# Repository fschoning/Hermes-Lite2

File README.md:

> **This fork: HL2 raw front end.** Experimental gateware that streams every raw ADC sample over the HL2's own
> gigabit Ethernet port, with a RISC-V CPU and a transmit interlock inside the FPGA. See the
> [release](https://github.com/fschoning/Hermes-Lite2/releases/tag/hl2-rawfront-release-v0.1),
> the [documentation](https://github.com/fschoning/Hermes-Lite2/blob/hl2-rawfront-release/docs/rawfront/README.md)
> and the [source branch](https://github.com/fschoning/Hermes-Lite2/tree/hl2-rawfront-release).

Hermes-Lite 2.x
===============

See the main [Hermes-Lite Web Page](http://www.hermeslite.com) for the latest links and details.

This is a work in progress to create a low-cost software defined amateur radio HF transceiver based on a [broadband modem chip](http://www.analog.com/en/broadband-products/broadband-codecs/ad9866/products/product.html) and the [Hermes SDR](http://openhpsdr.org/wiki/index.php?title=HERMES) project.

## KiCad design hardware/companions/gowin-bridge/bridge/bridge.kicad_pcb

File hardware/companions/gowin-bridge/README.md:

# gowin-bridge — Hermes Lite 2 SlimSAS bridge, rev D

**One design with two ends, on one board.** One schematic, one PCB, one BOM,
one project directory. The **radio end** plugs onto the Hermes-Lite 2; the
**Gowin end** plugs onto a Tang Mega 138K dock's J14. They are made together
and snapped apart. Two radio ends and one cable make a radio-to-radio link; a
radio end, a Gowin end and one cable make a radio-to-FPGA link.

The radio end:
A flat companion board that plugs onto the HL2's **DB1** (2×10), **DB12** (2×3)
and **CN1** (2×5 JTAG) headers and carries **one SlimSAS SFF-8654 8i
receptacle** on its front edge. A single $15 cable carries 16 differential
pairs and 16 sideband conductors.

| | |
|---|---|
| Board | radio end **64.50 × 64.88 mm**, 4 layer, 1.6 mm, HASL. HL2 x 70.00→134.50, y 73.37→138.25. The whole board, both ends, is **64.50 × 92.00 mm**, no rails, the ends joined by three mouse-bite tabs |
| Underside | 11.04 mm above the HL2's top surface (10.92 mm measured on the owner's radio), on 2.54 mm sockets and one M3 screw; holes over the radio's FPGA, AD9866 and T2 |
| Connector | Amphenol ICC **U10A474240T**, LCSC **C5432262** |
| Cable | 10Gtek **CAB-8654/8654-8i-P**, 8i to 8i, 0.5 m, **$15** |
| Lane rate | DDR at 153.6 MHz = **307.2 Mbit/s**, three lanes each way |
| Payload | **921.6 Mbit/s** each way = the complete raw 12-bit 76.8 MSPS ADC stream, plus a full-duplex auxiliary channel at the same rate |
| Parts | both ends: 184, of which **152 fitted**; 176 nets; **24 placed part numbers**, 16 Basic, 7 Extended and 1 Preferred Extended; eleven test points |
| Cost | **$162.43** for five assembled boards, both ends, delivered: **$32.49 per complete link** |
| State | schematic generated and validated; **prepared for Quilter**: fixed parts locked, everything else waiting off the board (`QUILTER.md`); **not placed, not routed** |

---

## The documents, and which to read first

| | |
|---|---|
| **`STATUS.md`** | **Start here.** What is built, what changed from rev C and why, the four numbers that were blocking the order, three corrections to the brief, six deliberate departures from it, everything unverified, and the next steps in order |
| `PINMAP.md` | **The pin contract.** Every HL2 header pin, all 74 connector contacts, the crossover, the lane and sideband maps, the AUXIO group, the enables, and the paste-ready Quartus block. Authoritative; `tools/check_netlist.py` asserts it |
| `DESIGN_NOTES.md` | Why, with the numbers. Data rates, the 2.5 V threshold problem and the part that does not exist, termination and edge rates, **the power budget**, **the ESD decision**, the mechanical argument, parts sourcing, the JTAG contention answer, and everything unverified |
| `COST.md` | The order total in the categories the fab actually bills, what could be cut and what it saves, and what is not verified in the numbers |
| `ROUTING.md` | The routing rules for whoever lays this out, in the order they matter |

---

## Files

```
bridge/                 the ONE KiCad project
  bridge.kicad_sch      schematic, ERC 0 violations
  bridge.kicad_pcb      fixed parts locked, the rest staged off the board;
                        placement regions and keepouts; DRC 0, parity 0
  bridge.kicad_pro      project file, with the differentialpair and Power
                        net classes
quilter-upload/         the three KiCad 10 files to upload to Quilter
  bridge-bom.csv        BOM with LCSC numbers and a Populate column
  gowin-bridge.kicad_sym, gowin-bridge.pretty/   project-local libraries
templates/              1:1 print templates for offering up to the radio
panel-endcap/           the re-cut front end panel - SEE THE WARNING BELOW
tools/
  gen_gowin_bridge.py   generates everything above from one netlist description
  check_netlist.py      asserts the pin maps, the crossover and the safety props
  check_geometry.py     asserts the locked parts, the land patterns and,
                        on a returned board, the placement and routing rules
  cost_model.py         computes the order total from the generated BOM and PCB
  kisexp.py             the KiCad s-expression reader/writer
```

**Anything that changes a net must be changed in `tools/gen_gowin_bridge.py`
and regenerated, never hand-edited in the KiCad files, and `PINMAP.md` must be
updated in the same commit.**

## To rebuild and validate

```
cd hardware/companions/gowin-bridge
python tools/gen_gowin_bridge.py
python tools/check_geometry.py     # must print OK
python tools/check_netlist.py      # must print OK
python tools/cost_model.py         # the order total
# bridge/bridge.kicad_dru is picked up by DRC: fast nets 3 mm from every edge

set KC=C:\Users\franz\AppData\Local\Programs\KiCad\10.0\bin\kicad-cli.exe
%KC% sch erc --severity-error -o bridge/bridge-erc.rpt bridge/bridge.kicad_sch
%KC% pcb drc --severity-error --schematic-parity --refill-zones ^
     -o bridge/bridge-drc.rpt bridge/bridge.kicad_pcb
```

---

## The front end panel

`panel-endcap/panel-endcap.kicad_pcb` (55 mm case, rev C) has the SlimSAS
opening at **panel x 120.30–144.30 = HL2 y 107.30–131.30**, centred on the
connector, 24.00 × 10.40 mm at 12.39–22.79 mm above the HL2's top surface.
Nine stock vent holes had to go where the opening landed; nine were put back
above it on 13 Sep 2026, so the vent area is the stock 73.7 mm². Order it
separately as a bare PCB. `G:/proj/Hermes-Lite2/franz-claude-analysis/HL2_END_PANEL.md`
has the derivation, clearances and strength check.

**Not compatible:** the repo's DB9 adapter board (`hardware/companions/db9/`)
cannot be fitted with this board; its wires land on DB1 pins our socket
covers. Run a Hardrock-50 from the N2ADR HL2 IO board instead
(`DESIGN_NOTES.md` §14.7).

## The Gowin end

A passive board: the same SlimSAS connector, 12 ESD arrays, 9 resistors and a
hand-fitted 2×18 onto J14 positions 5–40. Bank 4 of the Gowin FPGA drives and
receives true LVDS at its 3.3 V supply. Placed at the 40 mm case position.
`PINMAP.md` §11, `DESIGN_NOTES.md` §11, `gowin_end_j14.cst`.

## To order

JLCPCB, **Economic** assembly, **5 boards**, 4 layer, 1.6 mm, lead-free HASL,
green, 1 oz, delivered as a single PCB with the tabs unbroken. It is one
64.50 × 92.00 mm board with one outline and no rails; the two ends are joined
by three mouse-bite tabs. Ask JLCPCB first whether that counts as one design
(`DESIGN_NOTES.md` §13.2). Do not buy impedance control — `COST.md` §4 explains why.
`COST.md` §1 is the line-by-line.

Then hand-solder, per board: the DB1 2×10 socket and the DB12 2×3 socket and
the CN1 2×5 socket on the **underside**, the JTAG pass-through 2×5 header on
the **top**, and **the connector's four 2.2 mm shell tails**.

**Before any of that, buy one cable and ohmmeter it.** The whole one-design
argument rests on the cable crossing row A onto row B, and 10Gtek publish no
wiring diagram for this part. `STATUS.md` has the test.

**And do not fit or remove the board with the radio powered** — the hot-plug
inrush is about 22 A for 3.3 µs. It is on the silkscreen.

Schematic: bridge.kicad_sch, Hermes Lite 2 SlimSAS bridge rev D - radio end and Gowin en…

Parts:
C1, C2, C3, C4, C5, C6, C7, C8, C9, C10, C11, C12, C13, C14, C15, C16, C17, C18, C19, C21, C22, C23: 100nF; C_0402_1005Metric; LCSC C1525
C20: 1uF; C_0402_1005Metric; LCSC C52923
C24, C25, C26: 10uF; C_0805_2012Metric; LCSC C15850
C27: 10pF; C_0402_1005Metric; LCSC C32949
C28: 10nF; C_0402_1005Metric; LCSC C15195
C29: 100uF; CP_EIA-3528-21_Kemet-B; LCSC C16133
C30, C101: 10nF; C_0805_2012Metric; LCSC C1710; not fitted
D1, D2, D3, D4, D5, D6, D7, D8, D9, D10, D11, D12, D101, D102, D103, D104, D105, D106, D107, D108, D109, D110, D111, D112: TPD4E05U06; USON-10_2.5x1.0mm_P0.5mm; LCSC C138714
D13, D14: RB751V-40; D_SOD-323; LCSC C7502691
FB1: 120R/2A; L_0603_1608Metric; LCSC C14709
FB2: 120R/2A; L_0603_1608Metric; LCSC C14709; not fitted
FID1, FID2, FID3: Fiducial; Fiducial_1mm_Mask2mm
J1: SlimSAS 8i 74P R/A; SlimSAS_SFF-8654_8i_74P_RightAngle; LCSC C5432262
J2: DB1 2x10 socket; PinSocket_2x10_P2.54mm_Vertical; not fitted
J3: DB12 2x03 socket; PinSocket_2x03_P2.54mm_Vertical; not fitted
J4: CN1 2x05 socket; PinSocket_2x05_P2.54mm_Vertical; not fitted
J5: JTAG pass-through; PinHeader_2x05_P2.54mm_Vertical; not fitted
J101: SlimSAS 8i 74P R/A; SlimSAS_SFF-8654_8i_74P_RightAngle_M3; LCSC C5432262
J102: TANG J14 pos 5-40, 2x18; PinSocket_2x18_P2.54mm_Vertical; not fitted
L1: 4.7uH; L_Sunlord_SWPA4030S; LCSC C193025
Q1, Q2, Q3, Q4, Q5, Q6: AO3400A; SOT-23; LCSC C20917
R1, R37, R38, R39, R40, R41, R42, R43, R44: 100R; R_0402_1005Metric; LCSC C25076
R2: 470R; R_0402_1005Metric; LCSC C25117
R3, R4, R5, R6, R7, R8, R9, R10, R104, R106, R107, R108: 330R; R_0402_1005Metric; LCSC C25104
R11, R12, R13, R14, R15, R16, R17, R18, R19, R20, R28, R29, R30, R31, R32, R33, R34, R35, R36, R46, R47, R48, R49, R50, R51, R52, R102, R103, R109: 10k; R_0402_1005Metric; LCSC C25744
R21: 1k; R_0402_1005Metric; LCSC C11702; not fitted
R22, R23, R24, R25, R26: 0R; R_0402_1005Metric; LCSC C17168
R27, R101, R105: 1k; R_0402_1005Metric; LCSC C11702
R45: 100k; R_0402_1005Metric; LCSC C25741
R110, R111, R112, R113, R114, R115, R116: 100R; R_0402_1005Metric; LCSC C25076; not fitted
R117: 0R; R_0805_2012Metric; LCSC C17477
R_CLKSEL_A: 0R; R_0402_1005Metric; LCSC C17168
R_CLKSEL_B: 0R; R_0402_1005Metric; LCSC C17168; not fitted
R_DRVEN_ON: 0R; R_0402_1005Metric; LCSC C17168; not fitted
R_DRVEN_PRSNT: 0R; R_0402_1005Metric; LCSC C17168
R_LBYP: 0R; R_0805_2012Metric; LCSC C17477; not fitted
R_SHELL: 0R; R_0805_2012Metric; LCSC C17477
SL_VLVDS: 0R; R_0402_1005Metric; LCSC C17168; not fitted
TP1: TP_+3V3; TestPoint_Pad_D1.5mm
TP2: TP_+2V5; TestPoint_Pad_D1.5mm
TP3: TP_SB_PRSNT_IN; TestPoint_Pad_D1.5mm
TP4: TP_JTAG_EN_N; TestPoint_Pad_D1.5mm
TP5: TP_AUXIO_EN_N; TestPoint_Pad_D1.5mm
TP6: TP_AUXIO_OE_N; TestPoint_Pad_D1.5mm
TP7: TP_HL2_FWD_CLK; TestPoint_Pad_D1.5mm
TP8: TP_HL2_REV_CLK; TestPoint_Pad_D1.5mm
TP9: TP_GND; TestPoint_THTPad_D2.0mm_Drill1.0mm
TP10: TP_LINK_ALIVE; TestPoint_Pad_D1.5mm
TP101: TP_G_GND; TestPoint_THTPad_D2.0mm_Drill1.0mm
U1, U2, U3, U8, U9, U10, U11: SN74AVC4T245PW; TSSOP-16_4.4x5mm_P0.65mm; LCSC C81461
U4, U5: DS90LV047A; SOIC-16_3.9x9.9mm_P1.27mm; LCSC C206491
U6, U7: DS90LV048A; TSSOP-16_4.4x5mm_P0.65mm; LCSC C87137
U12: ME6211C25M5G; SOT-23-5; LCSC C194395

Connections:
+2V5: C1.1, C3.1, C6.1, C20.1, C23.1, C25.1, R16.2, R18.2, SL_VLVDS.2, TP2.1, U1.1 (VCCA), U1.2 (1DIR), U1.3 (2DIR), U2.1 (VCCA), U2.2 (1DIR), U2.3 (2DIR), U3.16 (VCCB), U12.5 (V_{OUT})
+3V3: C2.1, C4.1, C5.1, C7.1, C8.1, C9.1, C10.1, C11.1, C12.1, C13.1, C14.1, C15.1, C16.1, C17.1, C18.1, C19.1, C22.1, C24.1, C29.1, L1.2, R17.2, R19.2, R20.2, R27.2, R30.2, R32.2, R33.2, R34.2, R35.2, R46.2, R47.2, R48.2, R_DRVEN_ON.2, R_LBYP.2, TP1.1, U1.16 (VCCB), U2.16 (VCCB), U3.1 (VCCA), U3.2 (1DIR), U3.3 (2DIR), U4.4 (VCC), U5.4 (VCC), U6.13 (VCC), U6.16 (EN), U7.13 (VCC), U7.16 (EN), U8.1 (VCCA), U8.2 (1DIR), U8.3 (2DIR), U8.16 (VCCB), U9.1 (VCCA), U9.2 (1DIR), U9.3 (2DIR), U9.16 (VCCB), U10.1 (VCCA), U10.2 (1DIR), U10.3 (2DIR), U10.16 (VCCB), U11.1 (VCCA), U11.2 (1DIR), U11.3 (2DIR), U11.16 (VCCB), U12.1 (V_{IN}), U12.3 (CE)
AUXIO0_T: R3.2, U8.4 (1A1), U9.13 (1B1)
AUXIO1_T: R4.2, U8.5 (1A2), U9.12 (1B2)
AUXIO2_T: R5.2, U8.6 (2A1), U9.11 (2B1)
AUXIO3_T: R6.2, U8.7 (2A2), U9.10 (2B2)
AUXIO_EN_LA_N: Q1.2 (S), Q4.3 (D)
AUXIO_EN_N: Q4.2 (S), R19.1, TP5.1, U2.10 (2B2)
AUXIO_OE_N: Q1.3 (D), R20.1, TP6.1, U9.14 (2~OE), U9.15 (1~OE)
A_ADCD0_N: D4.2 (D1-), J1.A18, U4.13 (DOUT2-)
A_ADCD0_P: D4.1 (D1+), J1.A17, U4.14 (DOUT2+)
A_ADCD1_N: D5.2 (D1-), J1.A21, U4.12 (DOUT3-)
A_ADCD1_P: D5.1 (D1+), J1.A20, U4.11 (DOUT3+)
A_ADCD2_N: D6.2 (D1-), J1.A24, U4.9 (DOUT4-)
A_ADCD2_P: D6.1 (D1+), J1.A23, U4.10 (DOUT4+)
A_AUXCLK_N: D1.2 (D1-), J1.A3, U5.13 (DOUT2-)
A_AUXCLK_P: D1.1 (D1+), J1.A2, U5.14 (DOUT2+)
A_AUXDAT_N: D2.2 (D1-), J1.A6, U5.12 (DOUT3-)
A_AUXDAT_P: D2.1 (D1+), J1.A5, U5.11 (DOUT3+)
A_DUPCLK_N: D7.2 (D1-), J1.A33, U5.16 (DOUT1-)
A_DUPCLK_P: D7.1 (D1+), J1.A32, U5.15 (DOUT1+)
A_FWDCLK_N: D3.2 (D1-), J1.A15, U4.16 (DOUT1-)
A_FWDCLK_P: D3.1 (D1+), J1.A14, U4.15 (DOUT1+)
A_SPARE_N: D8.2 (D1-), J1.A36, U5.9 (DOUT4-)
A_SPARE_P: D8.1 (D1+), J1.A35, U5.10 (DOUT4+)
B_AUXCLK_N: D1.5 (D2-), J1.B3, R37.2, U7.4 (RIN2-)
B_AUXCLK_P: D1.4 (D2+), J1.B2, R37.1, U7.3 (RIN2+)
B_AUXDAT_N: D2.5 (D2-), J1.B6, R38.2, U7.5 (RIN3-)
B_AUXDAT_P: D2.4 (D2+), J1.B5, R38.1, U7.6 (RIN3+)
B_DUPCLK_N: D7.5 (D2-), J1.B33, R43.2, U7.1 (RIN1-)
B_DUPCLK_P: D7.4 (D2+), J1.B32, R43.1, U7.2 (RIN1+)
B_REVCLK_N: D3.5 (D2-), J1.B15, R39.2, U6.1 (RIN1-)
B_REVCLK_P: D3.4 (D2+), J1.B14, R39.1, U6.2 (RIN1+)
B_SPARE_N: D8.5 (D2-), J1.B36, R44.2, U7.8 (RIN4-)
B_SPARE_P: D8.4 (D2+), J1.B35, R44.1, U7.7 (RIN4+)
B_TXD0_N: D4.5 (D2-), J1.B18, R40.2, U6.4 (RIN2-)
B_TXD0_P: D4.4 (D2+), J1.B17, R40.1, U6.3 (RIN2+)
B_TXD1_N: D5.5 (D2-), J1.B21, R41.2, U6.5 (RIN3-)
B_TXD1_P: D5.4 (D2+), J1.B20, R41.1, U6.6 (RIN3+)
B_TXD2_N: D6.5 (D2-), J1.B24, R42.2, U6.8 (RIN4-)
B_TXD2_P: D6.4 (D2+), J1.B23, R42.1, U6.7 (RIN4+)
CN1_NC6: J4.6, J5.6
CN1_NC7: J4.7, J5.7
CN1_NC8: J4.8, J5.8
CN1_VTREF: J4.4, J5.4
DB1_3V3: C21.1, C26.1, FB1.1, J2.19, J2.20
DI_ADCD0: U1.12 (1B2), U4.3 (DIN2)
DI_ADCD1: U1.11 (2B1), U4.6 (DIN3)
DI_ADCD2: U1.10 (2B2), U4.7 (DIN4)
DI_AUXCLK: U2.13 (1B1), U5.3 (DIN2)
DI_AUXDAT: U2.12 (1B2), U5.6 (DIN3)
DI_FWDCLK: U1.13 (1B1), U4.2 (DIN1), U5.2 (DIN1), U11.6 (2A1)
DI_SPARE: R36.1, U5.7 (DIN4)
DRV_EN: R_DRVEN_ON.1, R_DRVEN_PRSNT.1, U4.1 (EN), U5.1 (EN)
GND: C1.2, C2.2, C3.2, C4.2, C5.2, C6.2, C7.2, C8.2, C9.2, C10.2, C11.2, C12.2, C13.2, C14.2, C15.2, C16.2, C17.2, C18.2, C19.2, C20.2, C21.2, C22.2, C23.2, C24.2, C25.2, C26.2, C28.2, C29.2, C30.2, D1.3 (GND), D1.8 (GND), D2.3 (GND), D2.8 (GND), D3.3 (GND), D3.8 (GND), D4.3 (GND), D4.8 (GND), D5.3 (GND), D5.8 (GND), D6.3 (GND), D6.8 (GND), D7.3 (GND), D7.8 (GND), D8.3 (GND), D8.8 (GND), D9.3 (GND), D9.8 (GND), D10.3 (GND), D10.8 (GND), D11.3 (GND), D11.8 (GND), D12.3 (GND), D12.8 (GND), D13.2 (A), J1.A1, J1.A4, J1.A7, J1.A10, J1.A13, J1.A16, J1.A19, J1.A22, J1.A25, J1.A28, J1.A31, J1.A34, J1.A37, J1.B1, J1.B4, J1.B7, J1.B10, J1.B13, J1.B16, J1.B19, J1.B22, J1.B25, J1.B28, J1.B31, J1.B34, J1.B37, J2.13, J2.14, J3.3, J3.4, J4.2, J4.10, J5.2, J5.10, Q2.2 (S), Q5.2 (S), Q6.2 (S), R2.2, R11.2, R12.2, R13.2, R14.2, R15.2, R21.2, R28.2, R29.2, R31.2, R36.2, R45.2, R49.2, R50.2, R51.2, R52.2, R_SHELL.2, TP9.1, U1.8 (GND), U1.9 (GND), U1.14 (2~OE), U1.15 (1~OE), U2.8 (GND), U2.9 (GND), U2.14 (2~OE), U2.15 (1~OE), U3.8 (GND), U3.9 (GND), U4.5 (GND), U4.8 (~EN), U5.5 (GND), U5.8 (~EN), U6.12 (GND), U7.12 (GND), U8.8 (GND), U8.9 (GND), U9.8 (GND), U9.9 (GND), U10.5 (1A2), U10.8 (GND), U10.9 (GND), U11.5 (1A2), U11.7 (2A2), U11.8 (GND), U11.9 (GND), U11.14 (2~OE), U12.2 (V_{SS})
G_A_AUXCLK_N: D101.2 (D1-), J101.A3, J102.23
G_A_AUXCLK_P: D101.1 (D1+), J101.A2, J102.24
G_A_AUXDAT_N: D102.2 (D1-), J101.A6, J102.17
G_A_AUXDAT_P: D102.1 (D1+), J101.A5, J102.18
G_A_DUPCLK_N: D107.2 (D1-), J101.A33, J102.1
G_A_DUPCLK_P: D107.1 (D1+), J101.A32, J102.2
G_A_REVCLK_N: D103.2 (D1-), J101.A15, J102.5
G_A_REVCLK_P: D103.1 (D1+), J101.A14, J102.6
G_A_SPARE_N: D108.2 (D1-), J101.A36
G_A_SPARE_P: D108.1 (D1+), J101.A35
G_A_TXD0_N: D104.2 (D1-), J101.A18, J102.31
G_A_TXD0_P: D104.1 (D1+), J101.A17, J102.32
G_A_TXD1_N: D105.2 (D1-), J101.A21, J102.33
G_A_TXD1_P: D105.1 (D1+), J101.A20, J102.34
G_A_TXD2_N: D106.2 (D1-), J101.A24, J102.35
G_A_TXD2_P: D106.1 (D1+), J101.A23, J102.36
G_B_ADCD0_N: D104.5 (D2-), J101.B18, J102.13, R113.2
G_B_ADCD0_P: D104.4 (D2+), J101.B17, J102.14, R113.1
G_B_ADCD1_N: D105.5 (D2-), J101.B21, J102.11, R114.2
G_B_ADCD1_P: D105.4 (D2+), J101.B20, J102.12, R114.1
G_B_ADCD2_N: D106.5 (D2-), J101.B24, J102.9, R115.2
G_B_ADCD2_P: D106.4 (D2+), J101.B23, J102.10, R115.1
G_B_AUXCLK_N: D101.5 (D2-), J101.B3, J102.19, R110.2
G_B_AUXCLK_P: D101.4 (D2+), J101.B2, J102.20, R110.1
G_B_AUXDAT_N: D102.5 (D2-), J101.B6, J102.21, R111.2
G_B_AUXDAT_P: D102.4 (D2+), J101.B5, J102.22, R111.1
G_B_DUPCLK_N: D107.5 (D2-), J101.B33, J102.27, R116.2
G_B_DUPCLK_P: D107.4 (D2+), J101.B32, J102.28, R116.1
G_B_FWDCLK_N: D103.5 (D2-), J101.B15, J102.15, R112.2
G_B_FWDCLK_P: D103.4 (D2+), J101.B14, J102.16, R112.1
G_B_SPARE_N: D108.5 (D2-), J101.B36
G_B_SPARE_P: D108.4 (D2+), J101.B35
G_GND: C101.2, D101.3 (GND), D101.8 (GND), D102.3 (GND), D102.8 (GND), D103.3 (GND), D103.8 (GND), D104.3 (GND), D104.8 (GND), D105.3 (GND), D105.8 (GND), D106.3 (GND), D106.8 (GND), D107.3 (GND), D107.8 (GND), D108.3 (GND), D108.8 (GND), D109.3 (GND), D109.8 (GND), D110.3 (GND), D110.8 (GND), D111.3 (GND), D111.8 (GND), D112.3 (GND), D112.8 (GND), J101.A1, J101.A4, J101.A7, J101.A10, J101.A13, J101.A16, J101.A19, J101.A22, J101.A25, J101.A28, J101.A31, J101.A34, J101.A37, J101.B1, J101.B4, J101.B7, J101.B10, J101.B13, J101.B16, J101.B19, J101.B22, J101.B25, J101.B28, J101.B31, J101.B34, J101.B37, J102.8, R102.2, R105.2, R109.2, R117.2, TP101.1
G_PRSNT_DRV: J102.26, R101.1
G_PRSNT_RD: J102.25, R103.2
G_SB_NC_A11: D110.1 (D1+), J101.A11
G_SB_NC_A12: D110.4 (D2+), J101.A12
G_SB_NC_A26: D111.1 (D1+), J101.A26
G_SB_NC_A27: D111.4 (D2+), J101.A27
G_SB_NC_B9: D109.5 (D2-), J101.B9
G_SB_NC_B11: D110.2 (D1-), J101.B11
G_SB_NC_B12: D110.5 (D2-), J101.B12
G_SB_NC_B26: D111.2 (D1-), J101.B26
G_SB_NC_B27: D111.5 (D2-), J101.B27
G_SB_NC_B29: D112.2 (D1-), J101.B29
G_SB_PRSNT_IN: D109.2 (D1-), J101.B8, R102.1, R103.1
G_SB_PRSNT_OUT: D109.1 (D1+), J101.A8, R101.2
G_SB_TCK_OUT: D109.4 (D2+), J101.A9, R104.2
G_SB_TDI_OUT: D112.4 (D2+), J101.A30, R107.2
G_SB_TDO_IN: D112.5 (D2-), J101.B30, R108.1, R109.1
G_SB_TMS_OUT: D112.1 (D1+), J101.A29, R106.2
G_SHELL: C101.1, J101.SH1 (SHELL1), J101.SH2 (SHELL2), J101.SH3 (SHELL3), J101.SH4 (SHELL4), R117.1
G_TCK_DRV: J102.30, R104.1, R105.1
G_TDI_DRV: J102.29, R107.1
G_TDO_RD: J102.3, R108.2
G_TMS_DRV: J102.4, R106.1
HL2_ADC_D0: J2.2, R11.1, U1.5 (1A2)
HL2_ADC_D1: J2.3, R12.1, U1.6 (2A1)
HL2_ADC_D2: J2.5, R13.1, U1.7 (2A2)
HL2_AUXIO_EN: J2.1, R18.1, U2.7 (2A2)
HL2_AUX_CLK_IN: J3.5, R22.2
HL2_AUX_CLK_OUT: J2.6, R14.1, U2.4 (1A1)
HL2_AUX_DAT_IN: J3.2, R23.2
HL2_AUX_DAT_OUT: J3.1, R15.1, U2.5 (1A2)
HL2_CWR: J2.10, R3.1
HL2_CWT: J2.12, R4.1
HL2_FWD_CLK: R1.2, R2.1, TP7.1, U1.4 (1A1)
HL2_FWD_CLK_RAW: J2.9, R1.1
HL2_JTAG_EN: J2.4, R16.1, U2.6 (2A1)
HL2_REV_CLK: J3.6, R_CLKSEL_A.2, R_CLKSEL_B.2, TP8.1
HL2_SCL1: J2.16, R5.1
HL2_SDA1: J2.18, R6.1
HL2_TX_D0: J2.11, R24.2
HL2_TX_D1: J2.15, R25.2
HL2_TX_D2: J2.17, R26.2
JTAG_EN_N: Q3.3 (D), R17.1, R21.1, TP4.1, U10.14 (2~OE), U11.15 (1~OE)
JTAG_EN_RAW_N: Q3.2 (S), U2.11 (2B1)
J_TCK: J4.1, J5.1, R7.2
J_TDI: J4.9, J5.9, R9.2
J_TDO: J4.3, J5.3, R10.1
J_TDO_T: R10.2, R48.1, U10.4 (1A1)
J_TMS: J4.5, J5.5, R8.2
LA_CLK: C27.1, U11.11 (2B1)
LA_PUMP: C27.2, D13.1 (K), D14.2 (A)
LINK_ALIVE: C28.1, D14.1 (K), Q2.1 (G), Q3.1 (G), Q4.1 (G), Q6.3 (D), R45.1, TP10.1
P3V3_FB: FB1.2, L1.1, R_LBYP.1
PRSNT_OE_N: Q5.3 (D), Q6.1 (G), R47.1, U8.14 (2~OE), U8.15 (1~OE), U10.15 (1~OE)
RX_AUXCLK: R51.1, U3.6 (2A1), U7.14 (ROUT2)
RX_AUXDAT: R52.1, U3.7 (2A2), U7.11 (ROUT3)
RX_DUPCLK: R50.1, U3.5 (1A2), U7.15 (ROUT1)
RX_EN_N: Q2.3 (D), R46.1, U3.14 (2~OE), U3.15 (1~OE), U6.9 (~EN), U7.9 (~EN)
RX_REVCLK: R49.1, U3.4 (1A1), U6.15 (ROUT1)
RX_TXD0: R24.1, U6.14 (ROUT2)
RX_TXD1: R25.1, U6.11 (ROUT3)
RX_TXD2: R26.1, U6.10 (ROUT4)
SB_AUXIO0_IN: D10.2 (D1-), J1.B11, R32.1, U9.4 (1A1)
SB_AUXIO0_OUT: D10.1 (D1+), J1.A11, U8.13 (1B1)
SB_AUXIO1_IN: D10.5 (D2-), J1.B12, R33.1, U9.5 (1A2)
SB_AUXIO1_OUT: D10.4 (D2+), J1.A12, U8.12 (1B2)
SB_AUXIO2_IN: D11.2 (D1-), J1.B26, R34.1, U9.6 (2A1)
SB_AUXIO2_OUT: D11.1 (D1+), J1.A26, U8.11 (2B1)
SB_AUXIO3_IN: D11.5 (D2-), J1.B27, R35.1, U9.7 (2A2)
SB_AUXIO3_OUT: D11.4 (D2+), J1.A27, U8.10 (2B2)
SB_NC9: D9.4 (D2+), J1.A9
SB_NC29: D12.1 (D1+), J1.A29
SB_PRSNT_IN: D9.2 (D1-), J1.B8, Q1.1 (G), Q5.1 (G), R28.1, R_DRVEN_PRSNT.2, TP3.1
SB_PRSNT_OUT: D9.1 (D1+), J1.A8, R27.1
SB_TCK_IN: D9.5 (D2-), J1.B9, R29.1, U10.6 (2A1)
SB_TCK_IN_B: R7.1, U10.11 (2B1)
SB_TDI_IN: D12.5 (D2-), J1.B30, R31.1, U11.4 (1A1)
SB_TDI_IN_B: R9.1, U11.13 (1B1)
SB_TDO_OUT: D12.4 (D2+), J1.A30, U10.13 (1B1)
SB_TMS_IN: D12.2 (D1-), J1.B29, R30.1, U10.7 (2A2)
SB_TMS_IN_B: R8.1, U10.10 (2B2)
SHELL: C30.1, J1.SH1 (SHELL1), J1.SH2 (SHELL2), J1.SH3 (SHELL3), J1.SH4 (SHELL4), R_SHELL.1
VLVDS: FB2.1, J2.7, J2.8
VLVDS_F: FB2.2, SL_VLVDS.1
X_AUXCLK25: R22.1, U3.11 (2B1)
X_AUXDAT25: R23.1, U3.10 (2B2)
X_DUPCLK25: R_CLKSEL_B.1, U3.12 (1B2)
X_REVCLK25: R_CLKSEL_A.1, U3.13 (1B1)

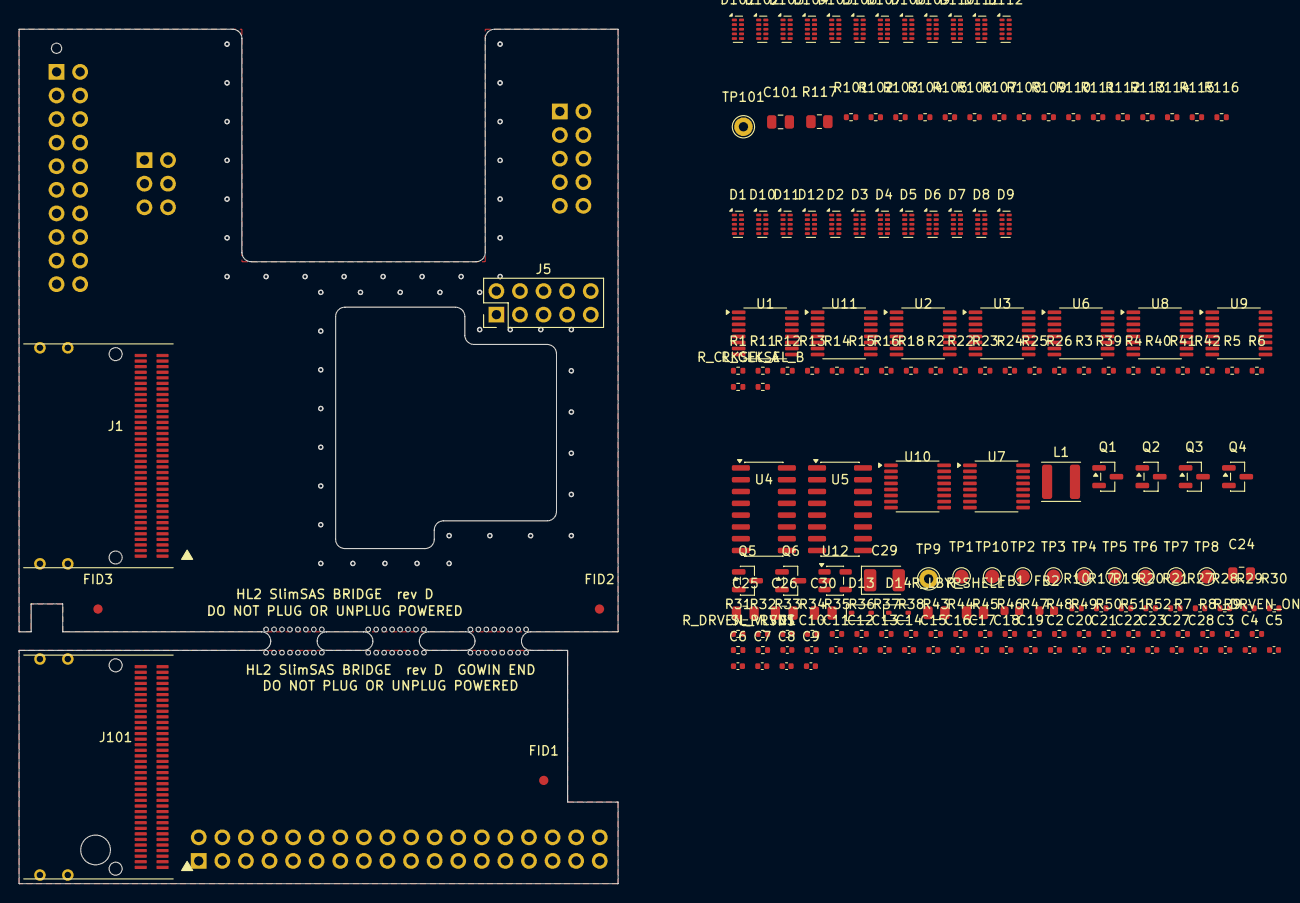
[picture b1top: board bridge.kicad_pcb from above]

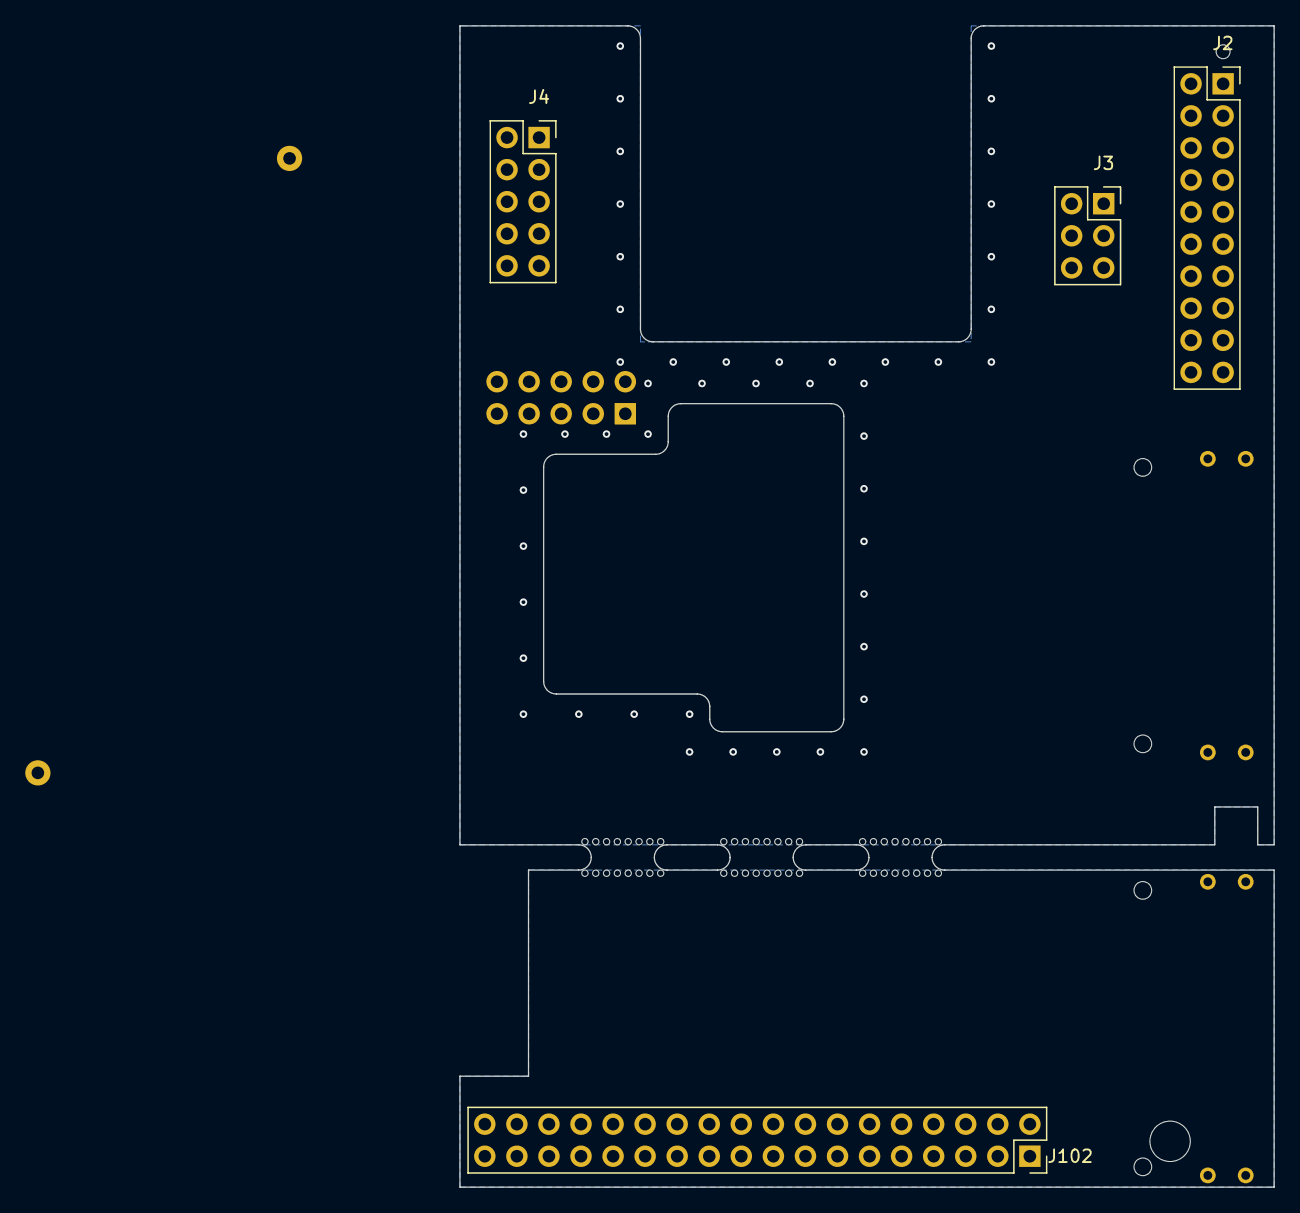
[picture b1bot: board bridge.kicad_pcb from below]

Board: 4 copper layers, 64.5 x 92.0 mm, 224 parts (4 on the bottom side), 176 nets, no tracks yet.

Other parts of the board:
MB1, MB2, MB3, MB4, MB5, MB6, MB7, MB8, MB9, MB10, MB11, MB12, MB13, MB14, MB15, MB16, MB17, MB18, MB19, MB20, MB21, MB22, MB23, MB24, MB25, MB26, MB27, MB28, MB29, MB30, MB31, MB32, MB33, MB34, MB35, MB36, MB37, MB38, MB39, MB40, MB41, MB42, MB43, MB44, MB45, MB46, MB47, MB48, MB49: Drill

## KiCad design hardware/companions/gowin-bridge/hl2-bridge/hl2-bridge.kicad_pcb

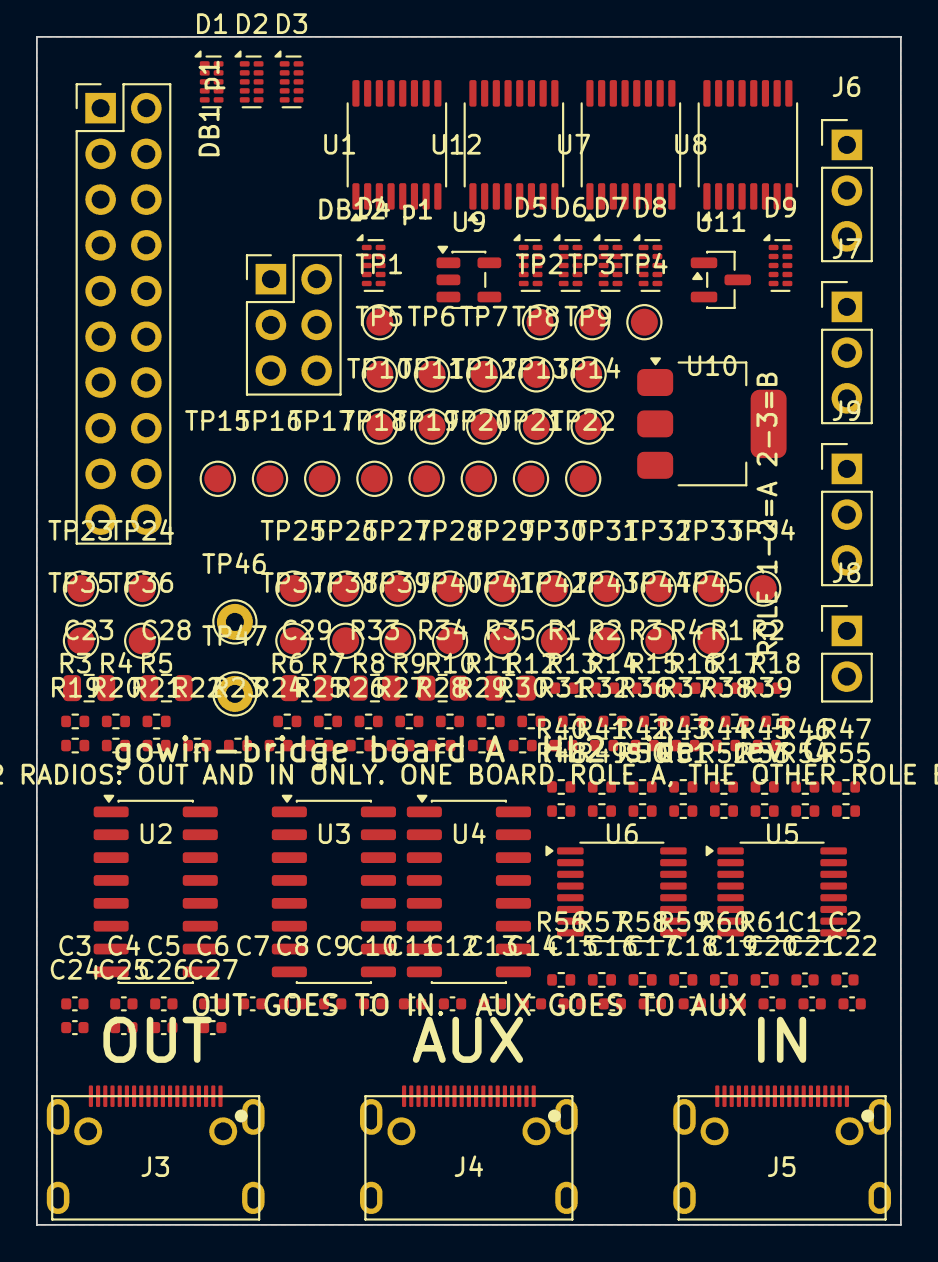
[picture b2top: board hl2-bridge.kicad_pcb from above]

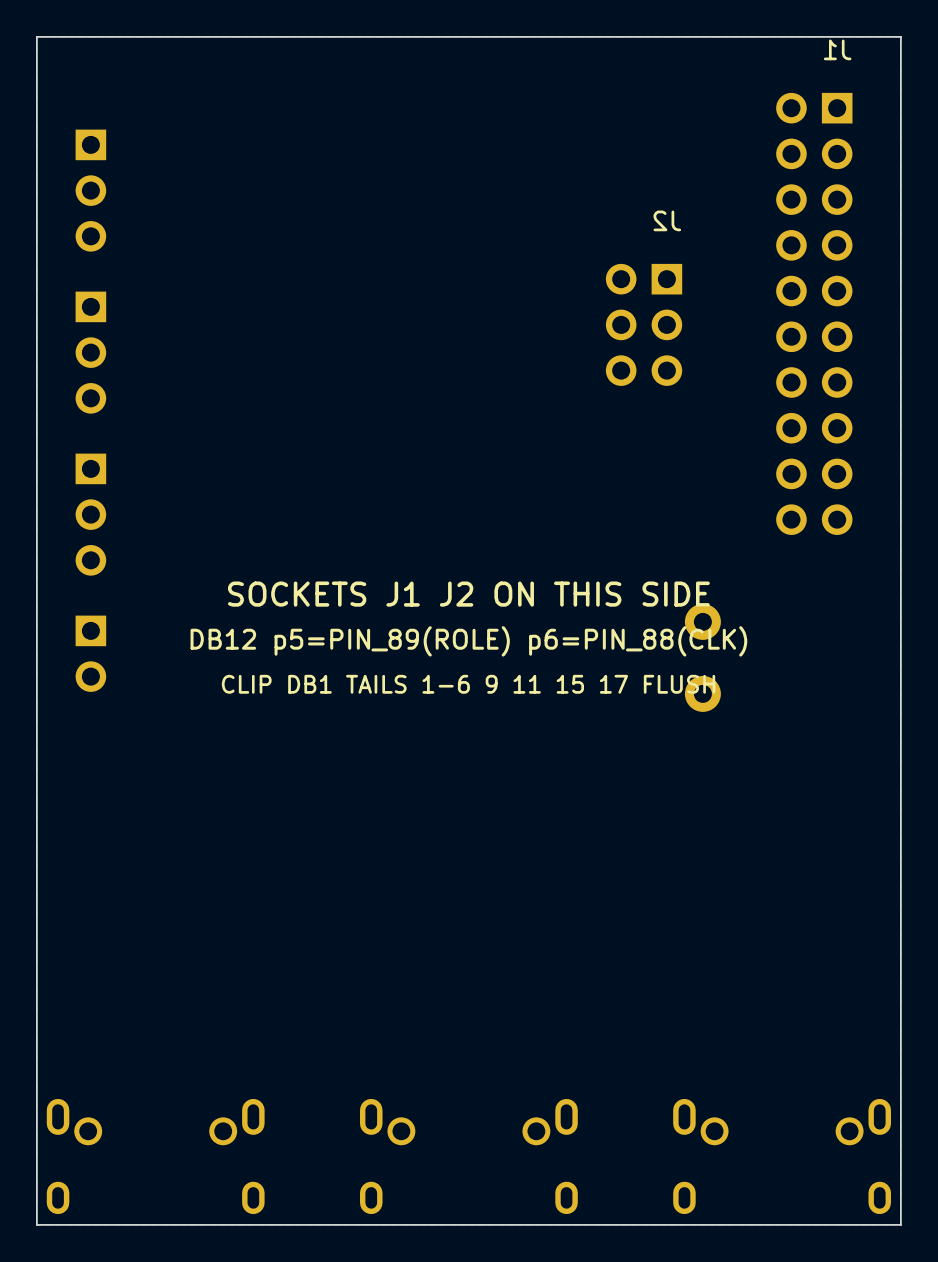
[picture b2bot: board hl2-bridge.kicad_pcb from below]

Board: 4 copper layers, 48.0 x 66.0 mm, 171 parts (2 on the bottom side), 98 nets, no tracks yet.

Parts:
C1, C2, C3, C4, C5, C6, C7, C8, C9, C10, C11, C12, C13, C14, C15, C16, C17, C18, C19, C20, C21, C22, C24, C26, C27: 100nF; C_0402_1005Metric
C23, C28, C29: 10uF; C_0805_2012Metric
C25: 1uF; C_0402_1005Metric
D1, D2, D3, D4, D5, D6, D7, D8, D9: TPD4E05U06; USON-10_2.5x1.0mm_P0.5mm
J1: DB1 2x10 stack-through; PinSocket_2x10_P2.54mm_Vertical
J2: DB12 2x03 socket; PinSocket_2x03_P2.54mm_Vertical
J3: OUT (mini HDMI); HDMI_C_Mini_19P_Horizontal_Hybrid
J4: AUX (mini HDMI); HDMI_C_Mini_19P_Horizontal_Hybrid
J5: IN (mini HDMI); HDMI_C_Mini_19P_Horizontal_Hybrid
J6: 3V3 SRC; PinHeader_1x03_P2.54mm_Vertical
J7: RX MODE; PinHeader_1x03_P2.54mm_Vertical
J8: GND CLIP; PinHeader_1x02_P2.54mm_Vertical
J9: ROLE; PinHeader_1x03_P2.54mm_Vertical
R1, R8, R9, R10, R11, R12, R13, R14, R15, R16, R17, R18, R19, R20, R21, R22, R23, R24, R31, R32, R36, R37, R41, R42, R46, R47, R51, R52: 0R; R_0402_1005Metric
R1#2, R2#2, R3#2, R4#2, R5, R6, R7, R27, R30, R56: 10k; R_0402_1005Metric
R2, R25, R26, R38, R43, R48, R53, R58, R59, R60, R61: 100R; R_0402_1005Metric
R3, R4: 330R; R_0402_1005Metric
R28, R29: 100k; R_0402_1005Metric
R33, R34, R35: 0R; R_0805_2012Metric
R39, R40, R44, R45, R49, R50, R54, R55, R57: 4k7; R_0402_1005Metric
TP1: TP_HL2_CLK_RAW; TestPoint_Pad_D1.5mm
TP2: TP_HL2_CLK; TestPoint_Pad_D1.5mm
TP3: TP_HL2_O_D0; TestPoint_Pad_D1.5mm
TP4: TP_HL2_O_D1; TestPoint_Pad_D1.5mm
TP5: TP_HL2_O_D2; TestPoint_Pad_D1.5mm
TP6: TP_HL2_AX_G1CLK; TestPoint_Pad_D1.5mm
TP7: TP_HL2_AX_G1DAT; TestPoint_Pad_D1.5mm
TP8: TP_HL2_AX_G2CLK; TestPoint_Pad_D1.5mm
TP9: TP_HL2_AX_G2DAT; TestPoint_Pad_D1.5mm
TP10: TP_HL2_SLOW_OUT; TestPoint_Pad_D1.5mm
TP11: TP_HL2_I_D0; TestPoint_Pad_D1.5mm
TP12: TP_HL2_I_D1; TestPoint_Pad_D1.5mm
TP13: TP_HL2_I_D2; TestPoint_Pad_D1.5mm
TP14: TP_HL2_INCLK; TestPoint_Pad_D1.5mm
TP15: TP_HL2_ROLE_IN; TestPoint_Pad_D1.5mm
TP16: TP_ROLE; TestPoint_Pad_D1.5mm
TP17: TP_ROLE_N; TestPoint_Pad_D1.5mm
TP18: TP_DRVI_O_CLK; TestPoint_Pad_D1.5mm
TP19: TP_DRVI_AX_CLK; TestPoint_Pad_D1.5mm
TP20: TP_DRVI_AX_D1; TestPoint_Pad_D1.5mm
TP21: TP_RXO_I_CLK; TestPoint_Pad_D1.5mm
TP22: TP_RXO_I_D0; TestPoint_Pad_D1.5mm
TP23: TP_RXO_I_D1; TestPoint_Pad_D1.5mm
TP24: TP_RXO_I_D2; TestPoint_Pad_D1.5mm
TP25: TP_RXO_AX_CLK; TestPoint_Pad_D1.5mm
TP26: TP_RXO_AX_D0; TestPoint_Pad_D1.5mm
TP27: TP_RXO_AX_D1; TestPoint_Pad_D1.5mm
TP28: TP_RXO_AX_D2; TestPoint_Pad_D1.5mm
TP29: TP_X_SP1; TestPoint_Pad_D1.5mm
TP30: TP_X_SP2; TestPoint_Pad_D1.5mm
TP31: TP_O_HPD; TestPoint_Pad_D1.5mm
TP32: TP_AX_HPD; TestPoint_Pad_D1.5mm
TP33: TP_I_HPD; TestPoint_Pad_D1.5mm
TP34: TP_AX_SLOW; TestPoint_Pad_D1.5mm
TP35: TP_I_SLOW; TestPoint_Pad_D1.5mm
TP36: TP_O_5V_PIN; TestPoint_Pad_D1.5mm
TP37: TP_AX_5V_PIN; TestPoint_Pad_D1.5mm
TP38: TP_I_5V_PIN; TestPoint_Pad_D1.5mm
TP39: TP_VBIAS; TestPoint_Pad_D1.5mm
TP40: TP_SCL1; TestPoint_Pad_D1.5mm
TP41: TP_SDA1; TestPoint_Pad_D1.5mm
TP42: TP_VLVDS; TestPoint_Pad_D1.5mm
TP43: TP_+3V3; TestPoint_Pad_D1.5mm
TP44: TP_+2V5; TestPoint_Pad_D1.5mm
TP45: TP_DB1_3V3; TestPoint_Pad_D1.5mm
TP46, TP47: TP_GND; TestPoint_THTPad_D2.0mm_Drill1.0mm
U1, U7, U8, U12: SN74AVC4T245PW; TSSOP-16_4.4x5mm_P0.65mm
U2, U3, U4: DS90LV047A; SOIC-16_3.9x9.9mm_P1.27mm
U5, U6: DS90LV048A; TSSOP-16_4.4x5mm_P0.65mm
U9: ME6211C25M5G; SOT-23-5
U10: AMS1117-3.3; SOT-223-3_TabPin2
U11: AO3400A; SOT-23

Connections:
+2V5: C11.1, C13.1, C20.1, C22.1, C25.1, R32.2, TP44.1, U1.1, U1.2, U1.3, U7.16, U8.16, U9.5, U12.1, U12.2, U12.3
+3V3: C10.1, C12.1, C14.1, C15.1, C16.1, C17.1, C18.1, C19.1, C21.1, C23.1, C24.1, C26.1, J6.2, J7.1, J9.1, R27.2, R30.2, R56.1, TP43.1, U1.16, U2.1, U2.4, U3.4, U4.4, U5.13, U5.16, U6.13, U6.16, U7.1, U7.2, U7.3, U8.1, U8.2, U8.3, U8.14, U9.1, U9.3, U12.16
AX_5V_PIN: D6.2, J4.18, TP37.1
AX_CLK_N: D4.1, J4.12, R58.2, U3.16, U6.1
AX_CLK_P: D3.5, J4.11, R58.1, U3.15, U6.2
AX_D0_N: D4.4, J4.9, R59.2, U3.13, U6.4
AX_D0_P: D4.2, J4.8, R59.1, U3.14, U6.3
AX_D1_N: D5.1, J4.6, R60.2, U4.16, U6.5
AX_D1_P: D4.5, J4.5, R60.1, U4.15, U6.6
AX_D2_N: D5.4, J4.3, R61.2, U4.13, U6.8
AX_D2_P: D5.2, J4.2, R61.1, U4.14, U6.7
AX_HPD: D6.1, J4.19, TP32.1
AX_SLOW: D5.5, J4.15, TP34.1
CLKDIV_MID: R3.2, R4.1
DB1_3V3: C27.1, J1.19, J1.20, J6.1, TP45.1
DRVI_AX_CLK: R12.2, TP19.1, U3.2, U12.13
DRVI_AX_D0: R13.2, U3.3, U12.12
DRVI_AX_D1: R14.2, TP20.1, U4.2, U12.11
DRVI_AX_D2: R15.2, U4.3, U12.10
DRVI_O_CLK: R8.2, TP18.1, U1.13, U2.2
DRVI_O_D0: R9.2, U1.12, U2.3
DRVI_O_D1: R10.2, U1.11, U2.6
DRVI_O_D2: R11.2, U1.10, U2.7
GND: C9.2, C10.2, C11.2, C12.2, C13.2, C14.2, C15.2, C16.2, C17.2, C18.2, C19.2, C20.2, C21.2, C22.2, C23.2, C24.2, C25.2, C26.2, C27.2, C28.2, C29.2, D1.3, D1.8, D2.3, D2.8, D3.3, D3.8, D4.3, D4.8, D5.3, D5.8, D6.3, D6.8, D7.3, D7.8, D8.3, D8.8, D9.3, D9.8, J1.13, J1.14, J2.3, J2.4, J3.1, J3.4, J3.7, J3.10, J3.13, J4.1, J4.4, J4.7, J4.10, J4.13, J5.1, J5.4, J5.7, J5.10, J5.13, J8.1, J8.2, J9.3, R1#2.2, R2#2.2, R3#2.2, R4.2, R4#2.2, R5.2, R6.2, R7.2, R26.2, R28.2, R29.2, R33.2, R34.2, R35.2, R57.2, TP46.1, TP47.1, U1.8, U1.9, U1.14, U1.15, U2.5, U2.8, U3.5, U3.6, U3.7, U3.8, U4.5, U4.6, U4.7, U4.8, U5.12, U6.9, U6.12, U7.8, U7.9, U7.15, U8.6, U8.7, U8.8, U8.9, U9.2, U10.1, U11.2, U12.8, U12.9, U12.14, U12.15
HL2_AX_G1CLK: J1.6, R4#2.1, R12.1, R21.2, TP6.1, U12.4
HL2_AX_G1DAT: J2.2, R5.1, R13.1, R22.2, TP7.1, U12.5
HL2_AX_G2CLK: R1.2, R6.1, R14.1, R23.2, TP8.1, U12.6
HL2_AX_G2CLK_HDR: J1.1, R1.1
HL2_AX_G2DAT: J1.4, R7.1, R15.1, R24.2, TP9.1, U12.7
HL2_CLK: R2.2, R3.1, R8.1, TP2.1, U1.4
HL2_CLK_RAW: J1.9, R2.1, TP1.1
HL2_INCLK: J2.6, R19.2, TP14.1
HL2_I_D0: J1.11, R16.2, TP11.1
HL2_I_D1: J1.15, R17.2, TP12.1
HL2_I_D2: J1.17, R18.2, TP13.1
HL2_O_D0: J1.2, R1#2.1, R9.1, TP3.1, U1.5
HL2_O_D1: J1.3, R2#2.1, R10.1, TP4.1, U1.6
HL2_O_D2: J1.5, R3#2.1, R11.1, TP5.1, U1.7
HL2_ROLE_IN: J2.5, R20.2, TP15.1
HL2_SLOW_OUT: J2.1, R25.1, TP10.1
I_5V_PIN: D9.1, J5.18, R31.1, TP38.1
I_CLK_N: C2.1, D6.5, J5.12, R37.1
I_CLK_P: C1.1, D6.4, J5.11, R36.1
I_CLK_RX_N: C2.2, R37.2, R38.2, R40.2, U5.1
I_CLK_RX_P: C1.2, R36.2, R38.1, R39.2, U5.2
I_D0_N: C4.1, D7.2, J5.9, R42.1
I_D0_P: C3.1, D7.1, J5.8, R41.1
I_D0_RX_N: C4.2, R42.2, R43.2, R45.2, U5.4
I_D0_RX_P: C3.2, R41.2, R43.1, R44.2, U5.3
I_D1_N: C6.1, D7.5, J5.6, R47.1
I_D1_P: C5.1, D7.4, J5.5, R46.1
I_D1_RX_N: C6.2, R47.2, R48.2, R50.2, U5.5
I_D1_RX_P: C5.2, R46.2, R48.1, R49.2, U5.6
I_D2_N: C8.1, D8.2, J5.3, R52.1
I_D2_P: C7.1, D8.1, J5.2, R51.1
I_D2_RX_N: C8.2, R52.2, R53.2, R55.2, U5.8
I_D2_RX_P: C7.2, R51.2, R53.1, R54.2, U5.7
I_HPD: D8.5, J5.19, J7.3, R27.1, TP33.1
I_SLOW: D8.4, J5.15, TP35.1
LDO3V3: C29.1, J6.3, U10.2
O_5V_PIN: D3.4, J3.18, TP36.1
O_CLK_N: D1.2, J3.12, U2.16
O_CLK_P: D1.1, J3.11, U2.15
O_D0_N: D1.5, J3.9, U2.13
O_D0_P: D1.4, J3.8, U2.14
O_D1_N: D2.2, J3.6, U2.12
O_D1_P: D2.1, J3.5, U2.11
O_D2_N: D2.5, J3.3, U2.9
O_D2_P: D2.4, J3.2, U2.10
O_HPD: D3.2, J3.19, R26.1, TP31.1
O_SLOW: D3.1, J3.15, R25.2
P5V_IN: C28.1, R31.2, U10.3
ROLE: J9.2, R29.1, TP16.1, U3.1, U7.5, U8.15, U11.1
ROLE_N: R30.1, TP17.1, U4.1, U7.14, U11.3
RXEN_N: J7.2, R28.1, U5.9
RXO_AX_CLK: TP25.1, U6.15, U8.4
RXO_AX_D0: TP26.1, U6.14, U8.5
RXO_AX_D1: TP27.1, U6.11, U7.6
RXO_AX_D2: TP28.1, U6.10, U7.7
RXO_I_CLK: TP21.1, U5.15, U7.4
RXO_I_D0: R16.1, TP22.1, U5.14
RXO_I_D1: R17.1, TP23.1, U5.11
RXO_I_D2: R18.1, TP24.1, U5.10
SCL1: J1.16, TP40.1
SDA1: J1.18, TP41.1
SHLD1: J3.SH, R33.1
SHLD2: J4.SH, R34.1
SHLD3: J5.SH, R35.1
VBIAS: C9.1, R39.1, R40.1, R44.1, R45.1, R49.1, R50.1, R54.1, R55.1, R56.2, R57.1, TP39.1
VLVDS: J1.7, J1.8, R32.1, TP42.1
X_AXG1CLK25: R21.1, U8.13
X_AXG1DAT25: R22.1, U8.12
X_AXG2CLK25: R23.1, U7.11
X_AXG2DAT25: R24.1, U7.10
X_INCLK25: R19.1, U7.13
X_ROLE25: R20.1, U7.12
X_SP1: TP29.1, U8.11
X_SP2: TP30.1, U8.10
